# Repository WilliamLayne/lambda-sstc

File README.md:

This project is based on Class-E Tesla Coil designs by Steve Ward and Labcoatz.   
https://stevehv.4hv.org/classEsstc.htm   
https://www.instructables.com/Making-the-Ultimate-Class-E-Musical-Tesla-Coil-Sin/ 

This project is a work in progress in collaboration with the Mines Maker Society for a kickoff workshop this coming fall semester. Expect build documentation sometime this May/June.

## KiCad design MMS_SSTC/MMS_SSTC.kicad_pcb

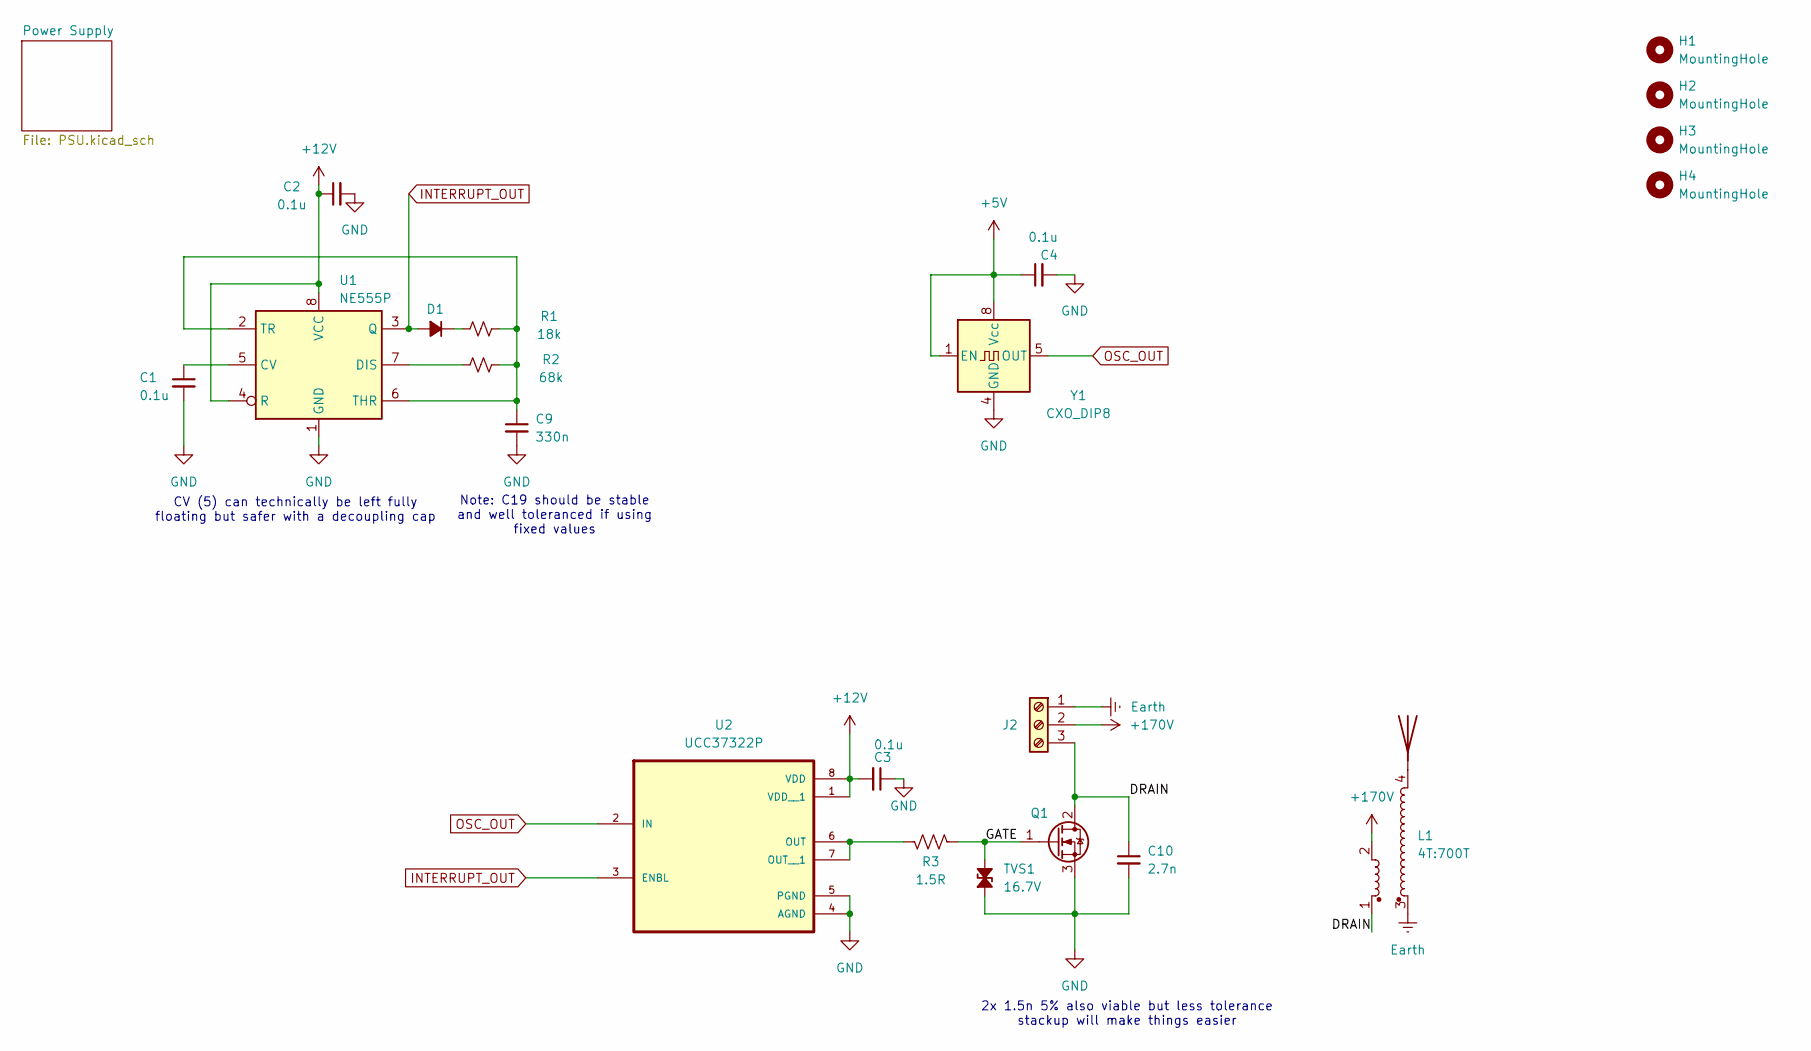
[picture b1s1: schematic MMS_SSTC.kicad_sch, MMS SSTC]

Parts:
AE1: Antenna
C1, C2, C3, C4: 0.1u; C_Disc_D3.0mm_W2.0mm_P2.50mm
C9: 330n; C_Rect_L7.2mm_W3.5mm_P5.00mm_FKS2_FKP2_MKS2_MKP2
C10: 2.7n; C_Rect_L13.0mm_W4.0mm_P10.00mm_FKS3_FKP3_MKS4
D1: D_Small_Filled; D_DO-35_SOD27_P7.62mm_Horizontal
H1, H2, H3, H4: MountingHole; MountingHole_3.2mm_M3
J2: Screw_Terminal_01x02; 691137710003
L1: 4T:700T
Q1: FQA8N100C; TO-247-3_Vertical
R1: 18k; R_Axial_DIN0204_L3.6mm_D1.6mm_P5.08mm_Horizontal
R2: 68k; R_Axial_DIN0204_L3.6mm_D1.6mm_P5.08mm_Horizontal
R3: 1.5R; R_Axial_DIN0204_L3.6mm_D1.6mm_P5.08mm_Horizontal
TVS1: 16.7V; D_DO-15_P10.16mm_Horizontal
U1: NE555P; DIP-8_W7.62mm_Socket
U2: UCC37322P; DIP-8_W7.62mm_Socket
Y1: CXO_DIP8; Oscillator_DIP-8

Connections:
+5V: C4.1, Y1.1 (EN), Y1.8 (Vcc); also elsewhere on the board
+12V: C2.1, C3.2, U1.4 (R), U1.8 (VCC), U2.1 (VDD__1), U2.8 (VDD); also elsewhere on the board
+170V: J2.2, L1.2; also elsewhere on the board
/DRAIN: C10.1, J2.3, L1.1, Q1.2 (D)
/GATE: Q1.1 (G), R3.1, TVS1.2 (A2)
Earth: J2.1, L1.3; also elsewhere on the board
GND: C1.2, C2.2, C3.1, C4.2, C9.2, C10.2, Q1.3 (S), TVS1.1 (A1), U1.1 (GND), U2.4 (AGND), U2.5 (PGND), Y1.4 (GND); also elsewhere on the board
INTERRUPT_OUT: D1.2 (A), U1.3 (Q), U2.3 (ENBL)
unnamed: AE1.1, L1.4
unnamed: D1.1 (K), R1.1
unnamed: C1.1, U1.5 (CV)
unnamed: R2.1, U1.7 (DIS)
unnamed: C9.1, R1.2, R2.2, U1.2 (TR), U1.6 (THR)
unnamed: R3.2, U2.6 (OUT), U2.7 (OUT__1)
OSC_OUT: U2.2 (IN), Y1.5 (OUT)

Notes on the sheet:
2x 1.5n 5% also viable but less tolerance stackup will make things easier
Note: C19 should be stable and well toleranced if using fixed values
CV (5) can technically be left fully floating but safer with a decoupling cap

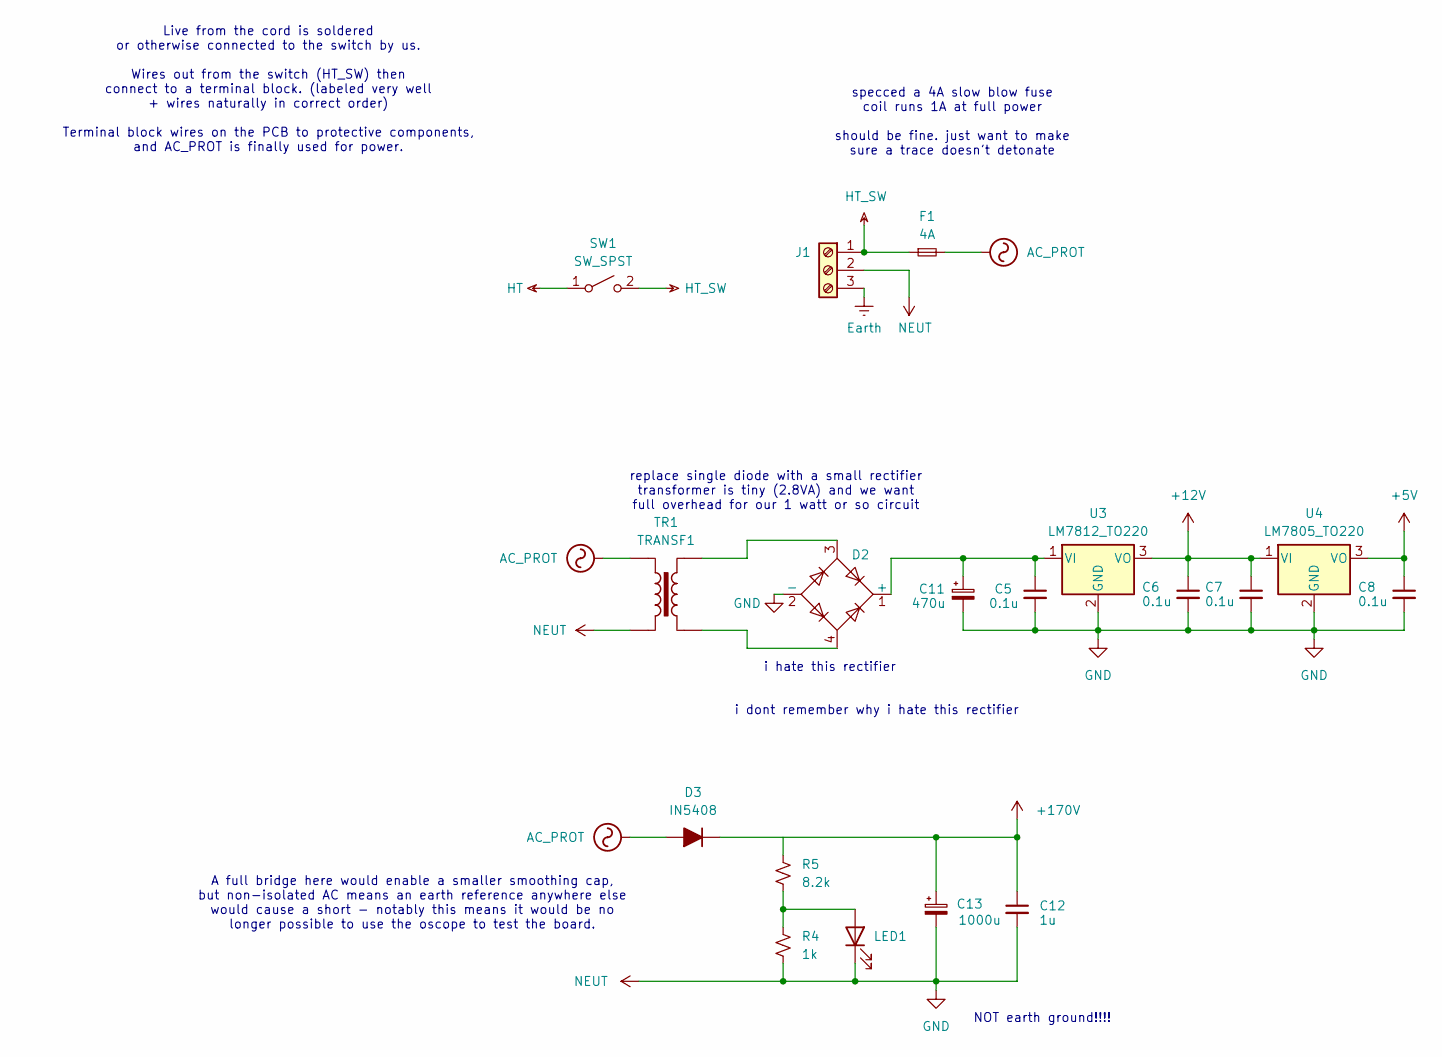
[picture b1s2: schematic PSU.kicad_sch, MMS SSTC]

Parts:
C5, C6, C7, C8: 0.1u; C_Disc_D3.0mm_W2.0mm_P2.50mm
C11: 470u; CP_Radial_D12.5mm_P5.00mm
C12: 1u; C_Rect_L18.0mm_W7.0mm_P15.00mm_FKS3_FKP3
C13: 1000u; CP_Radial_D22.0mm_P10.00mm_SnapIn
D2: DB105; Diode_Bridge_DIP-4_W7.62mm_P5.08mm
D3: IN5408; D_DO-201_P12.70mm_Horizontal
F1: 4A; R_Axial_DIN0411_L9.9mm_D3.6mm_P12.70mm_Horizontal
J1: Screw_Terminal_01x02; 691137710003
LED1: LED; LED_D5.0mm
R4: 1k; R_Axial_DIN0204_L3.6mm_D1.6mm_P5.08mm_Horizontal
R5: 8.2k; R_Axial_DIN0617_L17.0mm_D6.0mm_P5.08mm_Vertical
SW1: SW_SPST
TR1: TRANSF1; Transformer_Zettler_BV301S18028
U3: LM7812_TO220; TO-220-3_Vertical
U4: LM7805_TO220; TO-220-3_Vertical

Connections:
+5V: C8.1, U4.3 (VO); also elsewhere on the board
+12V: C6.1, C7.1, U3.3 (VO), U4.1 (VI); also elsewhere on the board
+170V: C12.1, C13.1, D3.1 (K); also elsewhere on the board
AC_PROT: D3.2 (A), F1.2, TR1.1
Earth: J1.3; also elsewhere on the board
GND: C5.2, C6.2, C7.2, C8.2, C11.2, C12.2, C13.2, D2.2 (-), J1.2, LED1.1 (K), R4.2, TR1.2, U3.2 (GND), U4.2 (GND); also elsewhere on the board
HT_SW: F1.1, J1.1, SW1.2 (B)
unnamed: C5.1, C11.1, D2.1 (+), U3.1 (VI)
unnamed: D2.3, TR1.4
unnamed: D2.4, TR1.3
unnamed: LED1.2 (A), R4.1, R5.2

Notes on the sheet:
NOT earth ground!!!!
i hate this rectifier
i dont remember why i hate this rectifier
Live from the cord is soldered or otherwise connected to the switch by us. Wires out from the switch (HT_SW) then connect to a terminal block. (labeled very well + wires naturally in correct order) Terminal block wires on the PCB to protective components, and AC_PROT is finally used for power.
replace single diode with a small rectifier transformer is tiny (2.8VA) and we want full overhead for our 1 watt or so circuit
specced a 4A slow blow fuse coil runs 1A at full power should be fine. just want to make sure a trace doesn't detonate
A full bridge here would enable a smaller smoothing cap, but non-isolated AC means an earth reference anywhere else would cause a short - notably this means it would be no longer possible to use the oscope to test the board.

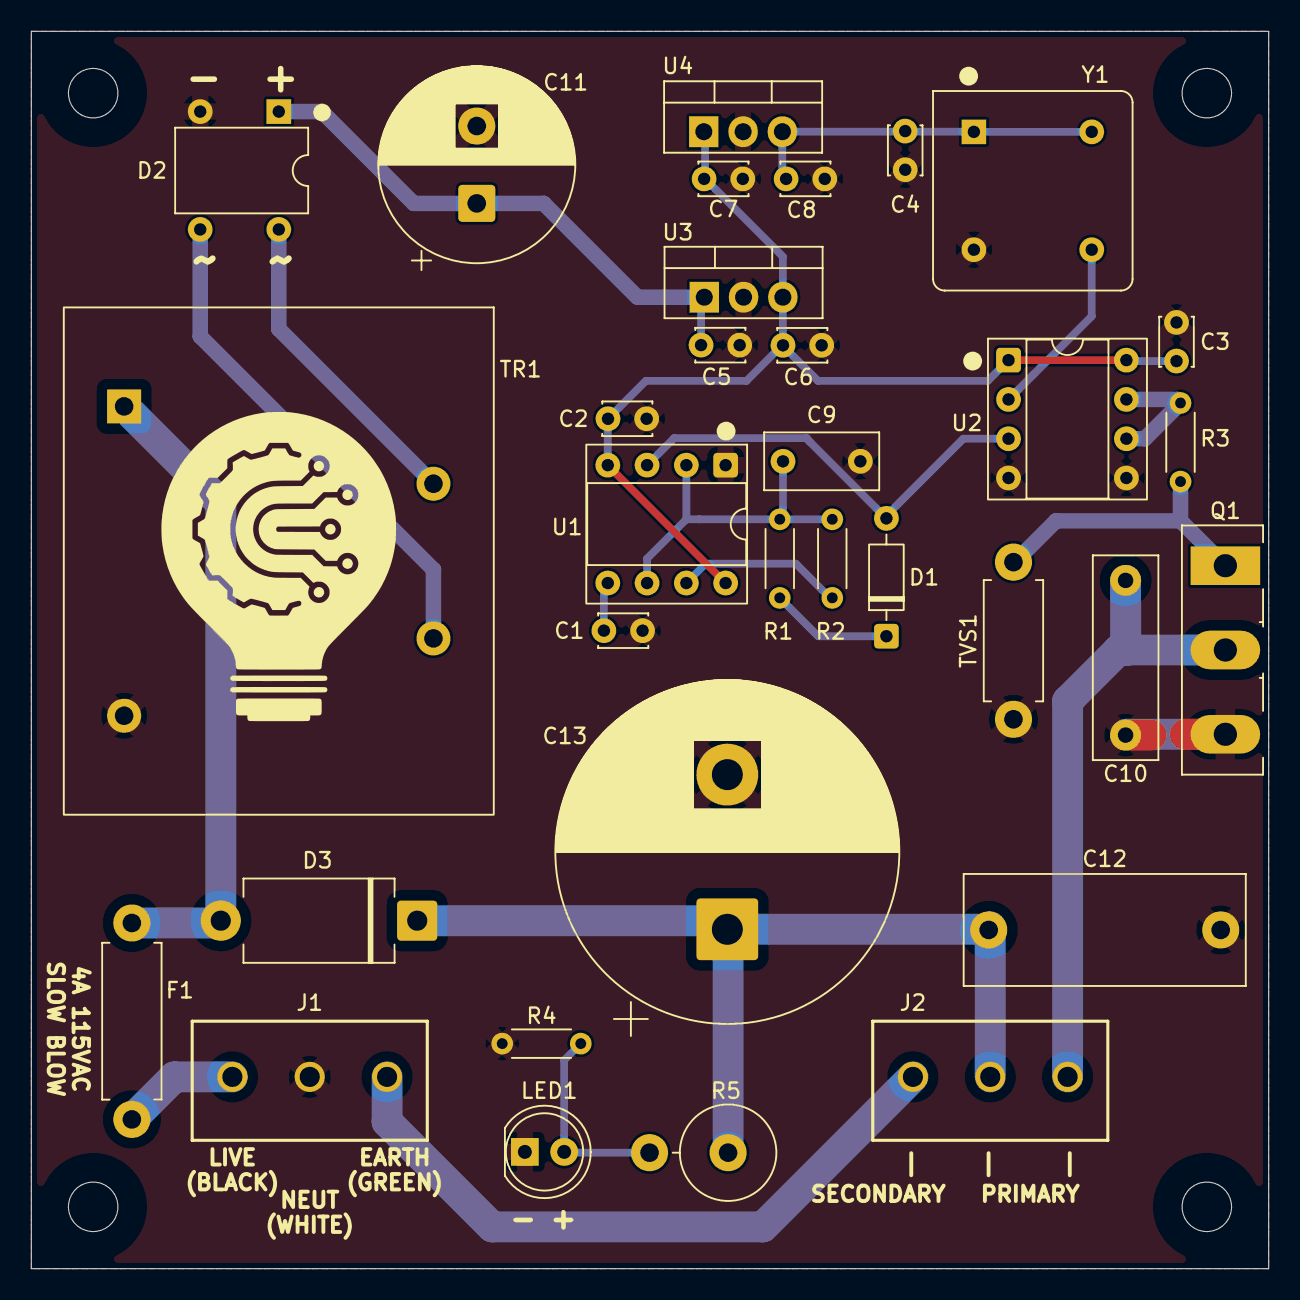
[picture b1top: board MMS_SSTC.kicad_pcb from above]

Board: 2 copper layers, 80.0 x 80.0 mm, 37 parts (0 on the bottom side), 20 nets.

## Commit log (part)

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2026-05-16 Add new WIP and Mk. 1 files from FA25 workshop. KiCad and circuit design is finalized/finalized+tweaks for pre-production test. CAD files are still outdated to Mk. 1 version.
2026-05-16 Add README and license
2026-05-16 Update PCB trace clearances
2026-05-16 Get CAD semi-finished, tweak PCB
2026-05-16 Update README.md
    grammar. stupid.
2026-05-22 Update heat sink and add zone clearance near screw holes
2026-06-07 Update CAD and drawings for CPP quote, switch to 3mm acrylic
2026-06-08 Update plots for final JLC order
2026-06-09 Clean up PCB after build test, add heat sink to assembly
